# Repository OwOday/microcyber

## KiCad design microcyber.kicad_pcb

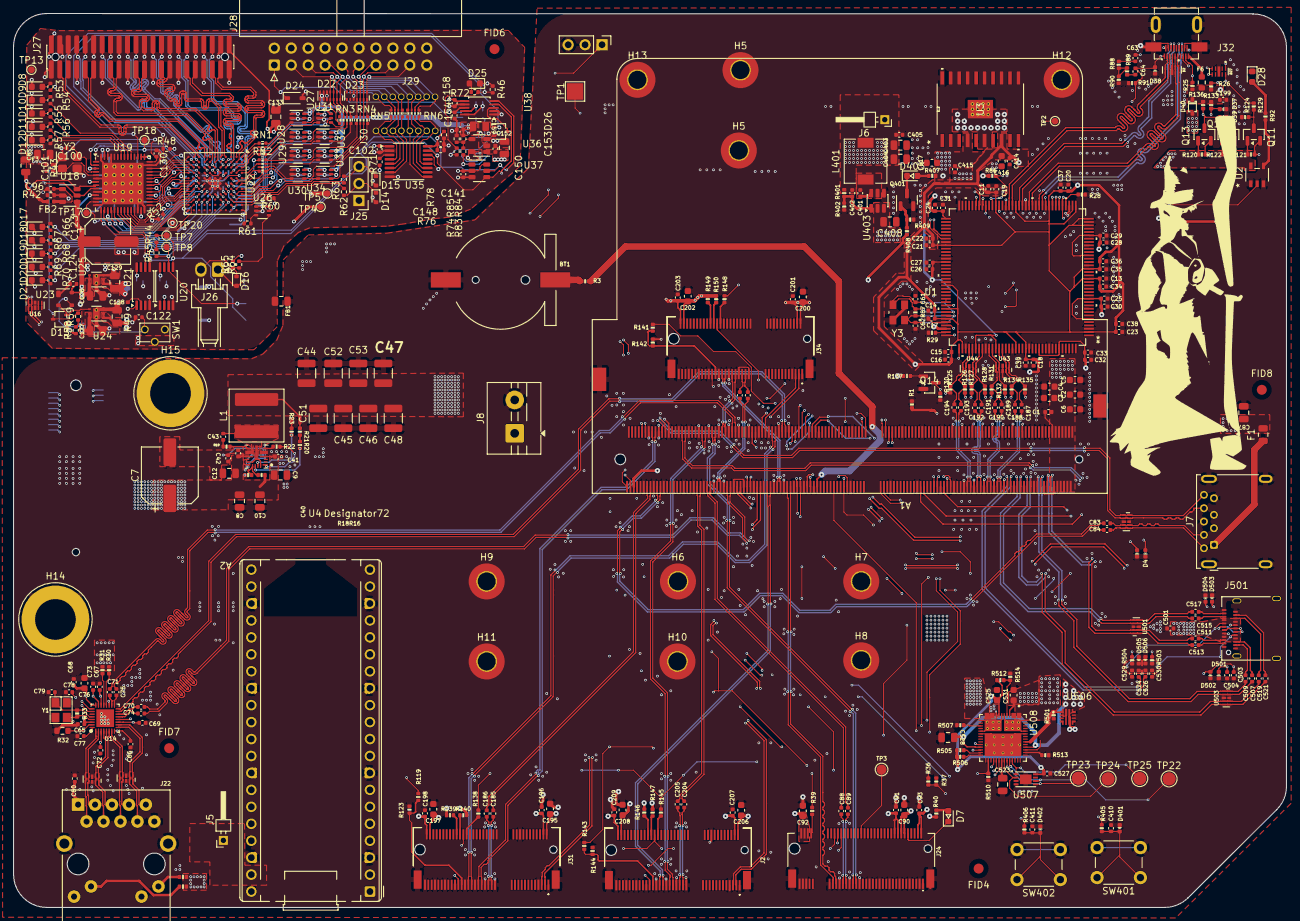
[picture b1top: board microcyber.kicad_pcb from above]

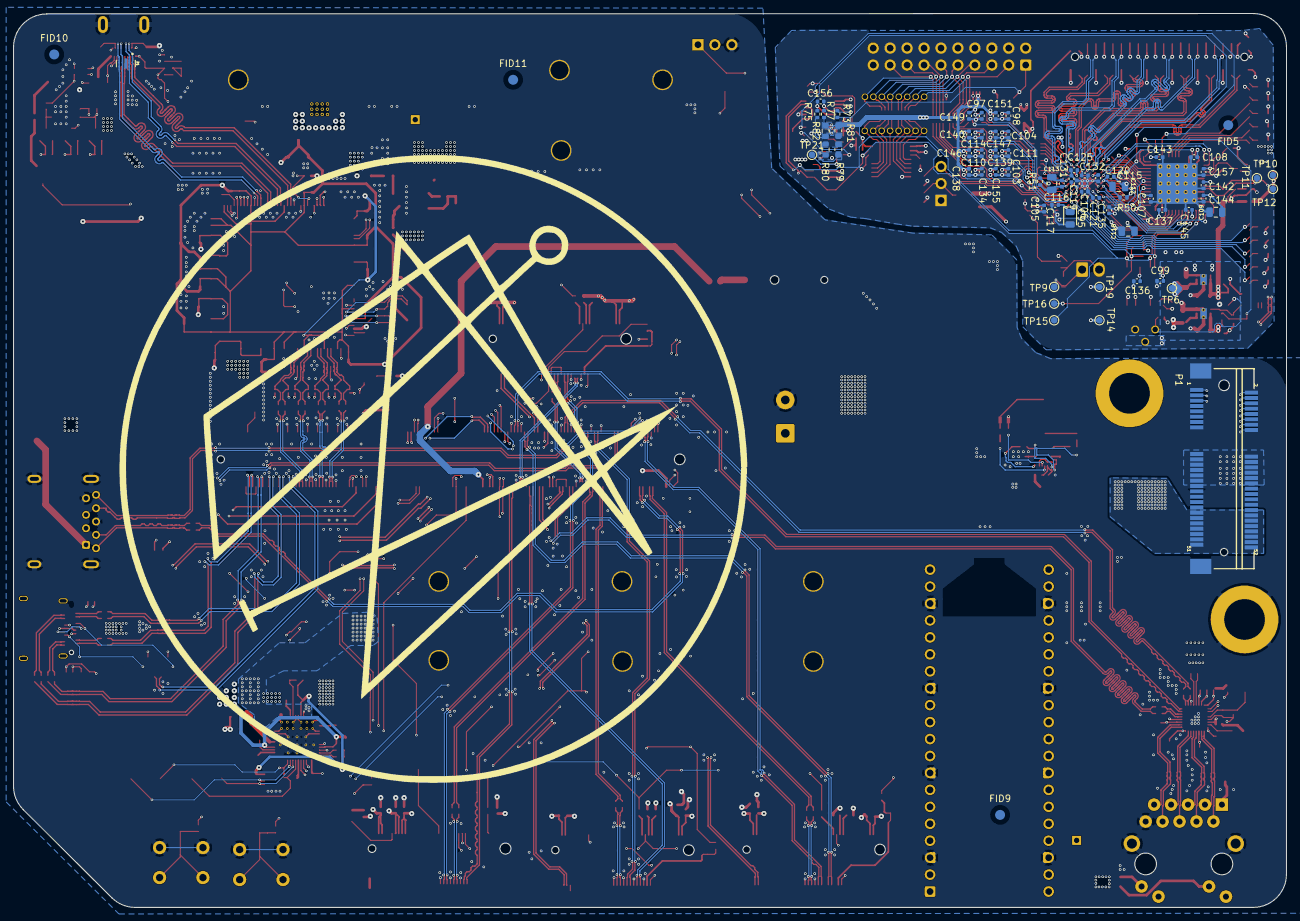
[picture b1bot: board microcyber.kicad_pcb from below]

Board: 6 copper layers, 190.8 x 134.0 mm, 497 parts (69 on the bottom side), 409 nets.

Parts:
A1: LattePanda_Mu; LattePanda_Module_H8.0mm_Horizontal
A2: RaspberryPi_Pico_W; RaspberryPi_Pico_Common_THT
BT1: Battery_Cell; Battery_Holder_CR1220_S8411-45R
C1, C43, C65, C66, C67, C68, C69, C70, C71, C72, C73, C74, C75, C77, C80, C83, C84, C91, C93, C96, C97, C98, C99, C102, C103, C104, C105, C106, C107, C108, C110, C111, C114, C115, C116, C117, C119, C120, C121, C122, C124, C125, C130, C131, C132, C134, C135, C136, C137, C138, C139, C140, C141, C142, C143, C144, C145, C146, C147, C148, C149, C150, C151, C153, C155, C156, C157, C158, C187, C188, C189, C190, C191, C192, C193, C194, C196, C198, C199, C201, C203, C207, C209, C401, C405, C414, C415, C501, C524, C526, C527: u1; C_0402_1005Metric
C2, C3, C4, C5, C6, C76, C90, C92, C195, C197, C200, C202, C206, C208: 10u; C_0603
C7: 330u; CP_Elec_8x11.9
C8, C9, C10, C12, C85, C87, C403, C404, C408, C523: 22u; C_0805_2012Metric
C11, C14, C16, C18, C20, C22, C24, C27, C29, C31, C33, C35, C37, C39: u1; C_0402
C13, C15, C17, C19, C21, C23, C25, C26, C28, C30, C32, C34, C36, C38: 10n; C_0402
C40, C41, C42, C410, C411: 1u; C_0402_1005Metric
C44, C45, C46, C47, C48, C51, C52, C53: 47u; C_1210_3225Metric
C49, C50, C88, C89, C185, C186, C204, C205, C511, C513, C519, C521: 220n; C_0402_1005Metric
C61, C62: 47p; C_0402
C63, C64: 1u; C_0402
C78, C79: 12p; C_0402_1005Metric
C95: 4u7; LED_0805_2012Metric
C100, C101: 9p; C_0402_1005Metric
C109, C112, C113, C118, C126, C127, C128, C129, C133, C152, C159, C528: 4u7; C_0805_2012Metric
C123: 150u; CP_Elec_6.3x5.9
C154: 1n 50V C0G; C_0402_1005Metric
C402, C503, C504, C529, C530: 47p; C_0402_1005Metric
C416, C417: 100u; C_0603
C507, C509, C515, C517: 330n; C_0402_1005Metric
C525, C531: 10u; C_0603_1608Metric
D1, D2, D27: RCLAMP0524PATCT; DIO_RCLAMP0524PATCT
D3, D4, D37, D38, D39: 0402ESDA-05N; D_0402_1005Metric
D7, D403: LED_G; LED_0603_1608Metric
D8, D25: GRN; LED_0603_1608Metric
D9, D19: WHT; LED_0603_1608Metric
D10, D17, D21: BLU; LED_0603_1608Metric
D11: ORA; LED_0603_1608Metric
D12: RED; LED_0603_1608Metric
D13: BAT54AW; SOT-323_SC-70
D14, D15, D16: ESD5Z5.0T1G; D_SOD-523
D18, D20: PNK; LED_0603_1608Metric
D22, D23: TPD6E05U06RVZR; UDFN-14_3.5x1.35mm_P0.5mm
D24: CDSOD323-T36S; D_SOD-323
D26: BAT54CW; SOT-323_SC-70
D28: LED; LED_0603_1608Metric
D40: 1N5819WS; D_SOD-323
D401, D402, D501, D502, D503, D504, D505, D506: ESD5V0B03; D_0402_1005Metric
F1: 6V/2A; Fuse_0805_2012Metric
F3: 6V/1A; Fuse_0805_2012Metric
F6: 6V/50mA; R_0603_1608Metric
FB1: 0; Fuse_0805_2012Metric
FB2: 600R, 0.5A; L_0402_1005Metric
FID4, FID5, FID6, FID7, FID8, FID9, FID10, FID11: Fiducial; Fiducial_1.5mm_Mask3mm
H5, H5#2, H6, H7, H8, H9, H10, H11, H12, H13: MountingHole_M2.0; MountingHole_2.7mm_Pad_TopOnly
H14, H15: MountingHole_Pad; Banana_Jack_1Pin
J1: Conn_01x03_Pin; PinHeader_1x03_P2.54mm_Vertical
J2, J31, J34: Bus_M.2_Socket_E; PCIe_M.2_Connectors_P=0.5mm_H=4.2mm_KeyE
J5, J6: Conn_01x01_Socket; PinHeader_1x01_P2.00mm_Horizontal
J7: USB3_A; USB3_A_Molex_48393-001
J8: Conn_01x02_Socket; TerminalBlock_MaiXu_MX126-5.0-02P_1x02_P5.00mm
J22: RJ45_RB1-125B8G1A; RJ45_UDE_RB1-125B8G1A
J24: Bus_M.2_Socket_M; PCIe_M.2_Connectors_P=0.5mm_H=4.2mm_KeyM
J25: AUX; PinHeader_1x03_P2.54mm_Vertical
J26: Conn_01x02; Molex_KK-254_1x02_P2.54mm_Horizontal
J27: PinHeader_2x22_P1.27mm; PinHeader_2x22_P1.27mm_Vertical__SMD
J28: IDC-Header_2x10_P2.54mm; IDC-Header_2x10_P2.54mm_Horizontal
J29, J30: Conn_01x08; PinSocket_1x08_P1.27mm_Vertical_DNP
J32: HDMI_D_1.4; HDMI_Micro-D_Molex_46765-2xxx
J501: USB_C_Receptacle; USB_C_Receptacle_Amphenol_12401610E4-2A
L1: 550nH; L_Coilcraft_XAL7070-XXX
L401: 6uH8; L_6.3x6.3_H3
NT1, NT3: NetTie_2; NetTie-2_SMD_Pad0.5mm
P1: 1775862-2; TE_1775862-2
Q11, Q401: 2N7002; SOT-23
Q12, Q13, Q14: 2SK3018; SOT-23
R1: 100K; R_0402
R3, R129: 1K; R_0402
R16: 200K; R_0402_1005Metric
R18, R401, R501, R503, R504, R507, R510: 100K; R_0402_1005Metric
R19, R20, R23, R512: 0; R_0402_1005Metric
R21: 10; R_0402_1005Metric
R22, R409, R506, R513: 10K; R_0402_1005Metric
R25, R26: 2k; R_0402
R28: 887; R_0402
R29: 500; R_0402
R30, R31, R139, R140, R146, R147, R149, R150: 10K; R_0402
R32: 2K49; R_0603_1608Metric
R33, R121: 1M; R_0402
R34, R35, R125, R126, R127, R128, R131, R132, R134, R135: 470; R_0402
R36, R119, R130, R141, R143: 0R/1%; R_0402_1005Metric
R37, R39, R123, R138, R142, R144, R145, R148: 0; R_0402
R40, R120, R122, R133, R136, R137: 2K2; R_0402
R42, R43: 5k1; R_0402_1005Metric
R44, R45, R54, R55, R60, R66, R67, R68, R69, R70, R76, R78: 2k2; R_0402_1005Metric
R46, R53, R65, R71, R74, R505: 10k; R_0402_1005Metric
R48, R52, R58, R59: 100k; R_0402_1005Metric
R49: DNP; R_0402_1005Metric_DNP
R50, R51: 100R; R_0402_1005Metric
R56, R57: 1k; R_0402_1005Metric
R61, R62, R63, R64: 47R; R_0402_1005Metric
R72: 20k; R_0402_1005Metric
R73: 470; R_0402_1005Metric
R75, R77: 4R7; R_0402_1005Metric
R79, R81: DNP; R_0603_1608Metric_DNP
R80: 0R33; R_0603_1608Metric
R82: 0R15; R_0603_1608Metric
R83: 49k9; R_0402_1005Metric
R84: 59k; R_0402_1005Metric
R85: 24k3; R_0402_1005Metric
R86: 47K; R_0402
R87: 390K; R_0402
R88, R89: 51; R_0402
R90: 5r1; R_0402
R91: 48K7; R_0402
R92: 220r; R_0402
R124: 21K5; R_0402
R402, R514: 19K1; R_0402_1005Metric
R405, R406, R407, R408: 1K; R_0402_1005Metric
RN1, RN2, RN3, RN4: 33R; R_Array_Convex_4x0402
RN5, RN6: 10k; R_Array_Convex_4x0402
SW1: RST; SW_Tactile_SPST_Angled_TC-1109DE
SW401, SW402: SW_Push; SW_PUSH_6mm
TP1: TestPoint; TestPoint_Pad_2.5x2.5mm
TP2: ALSB; TestPoint_Pad_D1.0mm
TP3: TestPoint; TestPoint_Pad_D1.5mm
TP4, TP14: 5V; TestPoint_Pad_D1.0mm
TP5, TP17, TP19: 3V3; TestPoint_Pad_D1.0mm
TP6, TP20: 1V2; TestPoint_Pad_D1.0mm
TP7, TP15: SDA; TestPoint_Pad_D1.0mm
TP8, TP16: SCL; TestPoint_Pad_D1.0mm
TP9: GND; TestPoint_Pad_D1.0mm
TP10: VBUS; TestPoint_Pad_D1.0mm
TP11: USBDM; TestPoint_Pad_D1.0mm
TP12: USBDP; TestPoint_Pad_D1.0mm
TP13: USBGND; TestPoint_Pad_D1.0mm
TP18: CLKREF; TestPoint_Pad_D1.0mm
TP21: VDAC; TestPoint_Pad_D1.0mm
TP22, TP23, TP24, TP25: TestPoint; TestPoint_Pad_D2.0mm
U1: ADV7623BSTZ; ST_144_ADI
U2: NC7SZ125M5; SC-74A-5_1P65X3P15_ONS
U3: TPPM0110DWPR; DWP20_3P81X2P79
U4: TPS548A23VANR; VAN0019A-MFG
U12, U13, U15, U16, U501, U503: ULC0524P; Diodes_UDFN-10_1.0x2.5mm_P0.5mm
U14: RTL8111H-CG-RH; QFN-32-1EP_4x4mm_P0.4mm_EP2.65x2.65mm
U18: TPD3S014; SOT-23-6
U19: CY7C68013A-56LTX; Cypress_QFN-56-1EP_8x8mm_P0.5mm_EP6.22x6.22mm_ThermalVias
U20: CAT24M01X; TSSOP-8_4.4x3mm_P0.65mm
U21: BL24C256A-SFRC; TSSOP-8_4.4x3mm_P0.65mm
U22: ICE40HX8K-BG121; BGA-121_9.0x9.0mm_Layout11x11_P0.8mm_Ball0.4mm_Pad0.35mm_NS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
U23: APX811-40UG-7; SOT-143
U24: TLV75533PDRVR; DFN-6-1EP_2x2mm_P0.65mm_EP1x1.6mm_ThermalVias
U25: TLV73312PQDRVR; DFN-6-1EP_2x2mm_P0.65mm_EP1x1.6mm_ThermalVias
U26, U27, U28, U29, U30, U31, U32, U33, U34: SN74LVC1T45DCKR; SOT-363_SC-70-6
U35: PCA6408APW; TSSOP-16_4.4x5mm_P0.65mm
U36: TPS73101DBV; SOT-23-5
U37: DAC081C081CIMK; SOT-23-6
U38: INA233; VSSOP-10_3x3mm_P0.5mm
U43, U44: TPAZ1023-04F; Diodes_UDFN-10_1.0x2.5mm_P0.5mm
U403: AP63200WU; TSOT-23-6
U506: LM73100RPWR; IC_LM73100RPWR
U507: AT25DN512C-MAHF-T; DFN-8-1EP_3x2mm_P0.5mm_EP1.75x1.45mm
U508: TPS65988DHRSHR; IC_TPS65987DDHRSHR
Y1: 25MHz; Crystal_SMD_3225-4Pin_3.2x2.5mm
Y2: 24M; Crystal_SMD_3225-4Pin_3.2x2.5mm
Y3: ABM8G-28.63636MHZ-18-D2Y-T; CRYSTAL_ABM8G_ABR

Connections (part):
5V_HDMI_VCC: C199.1, D40.1 (K), F6.1, R25.1, R26.1, R133.1, R136.1, U1.106 (5V_DETA)
+1V0: C65.2, C66.2, C67.2, C68.2, C72.2, C76.2, U14.3 (AVDD10), U14.8 (AVDD10), U14.22 (DVDD10), U14.24 (REGOUT), U14.30 (AVDD10)
+1V2_glasgow: C118.1, C119.1, C120.1, C121.1, C125.1, C129.1, R50.2, R51.2, TP6.1 (1_1), TP20.1 (1_1), U22.D4 (VCC), U22.D8 (VCC), U22.H4 (VCC), U22.H8 (VCC), U25.1 (OUT), U25.2 (NC)
+1V8: C11.1, C13.1, C14.1, C15.1, C16.1, C17.1, C18.1, C19.1, C20.1, C21.1, C22.1, C23.1, C34.1, C35.1, C36.1, C37.1, C38.1, C39.1, C414.2, C416.1, U1.2 (CVDD), U1.18 (DVDD), U1.21 (CVDD), U1.34 (CVDD), U1.36 (TXPVDD), U1.37 (TXPLVDD), U1.45 (TXAVDD), U1.55 (TXAVDD), U1.61 (DVDD), U1.81 (DVDD), U1.93 (DVDD), U1.100 (PVDD), U1.103 (PVDD), U1.110 (CVDD), U1.126 (DVDD), U1.129 (CVDD), U3.8 (1.8VOUT)
+3V3: C24.1, C25.1, C26.1, C27.1, C28.1, C29.1, C30.1, C31.1, C32.1, C33.1, C415.2, C417.1, Q11.1 (G), Q12.1 (G), Q13.1 (G), R86.2, R120.1, R121.1, R122.1, R407.2, U1.6 (TVDD), U1.12 (TVDD), U1.25 (TVDD), U1.31 (TVDD), U1.73 (DVDDIO), U1.86 (DVDDIO), U1.114 (TVDD), U1.120 (TVDD), U1.133 (TVDD), U1.139 (TVDD), U2.5 (VCC), U3.4 (3.3VOUT)
+3V3_TPS: C525.2, C527.2, R505.2, R506.2, R512.1, U507.8 (VCC), U508.9 (LDO_3V3)
+3V3_glasgow: C95.1, C97.1, C98.1, C99.1, C102.1, C103.1, C104.1, C105.1, C106.1, C107.1, C108.1, C109.1, C110.1, C111.1, C114.1, C117.1, C128.1, C131.1, C134.1, C135.1, C136.1, C137.1, C142.1, C143.1, C144.1, C145.1, C150.1, C157.1, C158.1, D13.2, J27.2, R44.2, R45.2, R48.2, R49.2, R53.1, R58.1, R65.2, R71.2, TP5.1 (1_1), TP19.1 (1_1), U19.3 (AVCC), U19.7 (AVCC), U19.11 (VCC), U19.17 (VCC), U19.27 (VCC), U19.32 (VCC), U19.43 (VCC), U19.44 (WAKEUP), U19.55 (VCC), U20.2 (A1), U20.8 (VCC), U21.1 (A0), U21.8 (VCC), U22.C10 (VPP_2V5), U22.D6 (VCCIO_0), U22.F8 (VCCIO_1), U22.H6 (VCCIO_2), U22.L11 (VCC_SPI), U24.1 (OUT), U24.2 (NC), U26.1 (VCCA), U26.6 (VCCB), U27.1 (VCCA), U28.1 (VCCA), U29.1 (VCCA), U30.1 (VCCA), U31.1 (VCCA), U32.1 (VCCA), U33.1 (VCCA), U34.1 (VCCA), U35.1 (VDD_I2C), U37.2 (VA), U37.6 (ADR0), U38.6 (VS)
+3V3_highpower: C44.2, C45.2, C46.2, C47.2, C48.2, C51.2, C52.2, C53.2, C69.2, C73.2, C77.2, C90.2, C91.2, C92.2, C93.2, C195.2, C196.2, C197.2, C198.1, C200.2, C201.2, C202.2, C203.2, C206.2, C207.2, C208.2, C209.2, C531.2, J2.2 (3.3V), J2.4 (3.3V), J2.72 (3.3V), J2.74 (3.3V), J24.2 (3.3V), J24.4 (3.3V), J24.12 (3.3V), J24.14 (3.3V), J24.16 (3.3V), J24.18 (3.3V), J24.70 (3.3V), J24.72 (3.3V), J24.74 (3.3V), J31.2 (3.3V), J31.4 (3.3V), J31.72 (3.3V), J31.74 (3.3V), J34.2 (3.3V), J34.4 (3.3V), J34.72 (3.3V), J34.74 (3.3V), L1.2, NT1.2, R30.1, R31.1, R34.2, R35.2, R40.2, R139.2, R140.1, R146.2, R147.1, R149.2, R150.1, U14.11 (AVDD33), U14.23 (VDDREG), U14.32 (AVDD33), U508.5 (VIN_3V3)
+5V: C85.2, C87.2, C402.1, C403.2, C404.2, C405.1, C528.2, D40.2 (A), F1.1, F3.1, J6.1 (Pin_1_1), L401.2, R401.2, U3.6 (5VCC), U506.5 (IN), U508.25 (PP1_CABLE), U508.46 (PP2_CABLE)
+5V_glasgow: C123.1, C124.1, C126.2, C127.2, C152.1, C153.1, TP4.1 (1_1), TP14.1 (1_1), U18.4 (OUT), U23.4 (VCC), U24.5 (NC), U24.6 (IN), U25.4 (EN), U25.5 (NC), U25.6 (IN), U36.1 (IN)
+12V: A1.250 (VIN), A1.251 (VIN), A1.252 (VIN), A1.253 (VIN), A1.254 (VIN), A1.255 (VIN), A1.256 (VIN), A1.257 (VIN), A1.258 (VIN), A1.259 (VIN), A1.260 (VIN), C1.1, C2.2, C3.2, C4.2, C5.2, C6.2, C7.1, C8.1, C9.1, C10.1, C12.1, C40.1, C41.1, C408.2, H15.1 (1_1), P1.38 (USB_D+/RES), P1.39 (+3.3VAUX/+3.3V3), P1.40 (GND10), P1.41 (+3.3VAUX/+3.3V4), P1.42 (~LED_WWAN/RES), P1.43 (GND/NC), P1.44 (~LED_WLAN/RES), P1.45 (RES/VENDOR1), P1.46 (~LED_WPAN/RES), P1.47 (RES/VENDOR2), P1.48 (+1.5V2), P1.49 (RES/DA/DSS), P1.50 (GND12), P1.51 (RES/DETECT), P1.52 (+3.3VAUX/+3.3V5), R16.1, U4.4 (VIN), U4.12 (VIN), U403.2 (EN), U403.3 (IN)
+BATT: A1.115 (VBAT), R3.1
/CLKREQ3: A1.100 (~CLKREQ3), R36.1, R119.1, R141.1, R143.1
/Ethernet/GbE_PCIe_CLK+: A1.94 (REFCLK4+), U14.15 (REFCLK_P)
/Ethernet/GbE_PCIe_CLK-: A1.96 (REFCLK4-), U14.16 (REFCLK_N)
/Ethernet/GbE_PCIe_RX+: A1.64 (HSIO6_RX+), C75.2
/Ethernet/GbE_PCIe_RX-: A1.66 (HSIO6_RX-), C71.2
/Ethernet/GbE_PCIe_TX+: A1.61 (HSIO6_TX+), C74.2
/Ethernet/GbE_PCIe_TX-: A1.63 (HSIO6_TX-), C70.2
/Ethernet/HSI+: C74.1, U14.13 (HSIP)
/Ethernet/HSI-: C70.1, U14.14 (HSIN)
/Ethernet/HSO+: C75.1, U14.17 (HSOP)
/Ethernet/HSO-: C71.1, U14.18 (HSON)
/Ethernet/LED1_1000: J22.L4, U14.26 (LED1)
/Ethernet/LED2_ACT: J22.L2, U14.25 (LED2)
/Ethernet/MDI0+: J22.R2 (TD1+), U13.5, U13.6 (NC), U14.1 (MDIP0)
/Ethernet/MDI0-: J22.R3 (TD1-), U13.4, U13.7 (NC), U14.2 (MDIN0)
/Ethernet/MDI1+: J22.R4 (TD2+), U13.2, U13.9 (NC), U14.4 (MDIP1)
/Ethernet/MDI1-: J22.R5 (TD2-), U13.1, U13.10 (NC), U14.5 (MDIN1)
/Ethernet/MDI2+: J22.R6 (TD3+), U12.5, U12.6 (NC), U14.6 (MDIP2)
/Ethernet/MDI2-: J22.R7 (TD3-), U12.4, U12.7 (NC), U14.7 (MDIN2)
/Ethernet/MDI3+: J22.R8 (TD4+), U12.2, U12.9 (NC), U14.9 (MDIP3)
/Ethernet/MDI3-: J22.R9 (TD4-), U12.1, U12.10 (NC), U14.10 (MDIN3)
/Ethernet/~CLKREQ4: A1.102 (~CLKREQ4), U14.12 (CLKREQB)
/GPIO_1: A2.21 (GPIO16), P1.4 (GND2)
/GPIO_2: A2.22 (GPIO17), P1.6 (1.5V/+1.5V)
/GPIO_3: A2.24 (GPIO18), P1.8 (UIM_PWR/RES)
/GPIO_4: A2.25 (GPIO19), P1.10 (UIM_DATA/RES)
/GPIO_5: A2.26 (GPIO20), P1.12 (UIM_CLK/RES)
/GPIO_6: A2.27 (GPIO21), P1.14 (UIM_RESET/RES)
/GPIO_7: A2.29 (GPIO22), P1.16 (UIM_VPP/RES)
/GPIO_8: A2.20 (GPIO15), P1.2 (3.3VAUX/+3.3V1)
/HDMI/CEC_STUB: D27.5, J32.15 (CEC)
/HDMI/DDC_SCL: D27.6, D37.2 (A2), J32.17 (SCL), Q12.3 (D), R25.2, R133.2, U1.43 (TXDDC_SDA), U1.109 (DDCA_SCL)
/HDMI/DDC_SDA: D27.1, D39.2 (A2), J32.18 (SDA), Q13.3 (D), R26.2, R136.2, U1.44 (TXDDC_SCL), U1.108 (DDCA_SDA)
/HDMI/DDI_B_DDC_SCL: A1.171 (DDIB_DDC_SCL), Q12.2 (S), R122.2
/HDMI/DDI_B_DDC_SDA: A1.169 (DDIB_DDC_SDA), Q13.2 (S), R120.2
/HDMI/DDI_B_HPD: A1.183 (DDIB_HPD), Q11.2 (S), R121.2
/HDMI/DDI_B_TX0+: A1.217 (DDIB_TX0+), C187.1
/HDMI/DDI_B_TX0-: A1.215 (DDIB_TX0-), C188.1
/HDMI/DDI_B_TX1+: A1.211 (DDIB_TX1+), C189.1
/HDMI/DDI_B_TX1-: A1.209 (DDIB_TX1-), C190.1
/HDMI/DDI_B_TX2+: A1.205 (DDIB_TX2+), C191.1
/HDMI/DDI_B_TX2-: A1.203 (DDIB_TX2-), C192.1
/HDMI/DDI_B_TX3+: A1.199 (DDIB_TX3+), C193.1
/HDMI/DDI_B_TX3-: A1.197 (DDIB_TX3-), C194.1
/HDMI/HDMI_TX0+: D2.2, D2.9, J32.9 (D0+), U1.51 (TX0+)
/HDMI/HDMI_TX0-: D2.1, D2.10, J32.11 (D0-), U1.50 (TX0-)
/HDMI/HDMI_TX1+: D1.1, D1.10, J32.6 (D1+), U1.54 (TX1+)
/HDMI/HDMI_TX1-: D1.2, D1.9, J32.8 (D1-), U1.53 (TX1-)
/HDMI/HDMI_TX2+: D2.5, D2.6, J32.3 (D2+), U1.57 (TX2+)
/HDMI/HDMI_TX2-: D2.4, D2.7, J32.5 (D2-), U1.56 (TX2-)
/HDMI/HDMI_TXC+: D1.4, D1.7, J32.12 (CK+), U1.48 (TXC+)
/HDMI/HDMI_TXC-: D1.5, D1.6, J32.14 (CK-), U1.47 (TXC-)
/HDMI/HDMI_TX_RESERVED: C63.2, J32.2 (UTILITY/HEAC+), U1.42 (ARC+)
/HDMI/HPD: C64.2, D27.10, D38.2 (A2), J32.1 (HPD/HEAC-), R91.1, R129.2, U1.41 (HPD_ARC-), U1.105 (HP_CTRLA), U2.2 (A)
/HDMI/OSD_CS: A2.2 (GPIO1), U1.65 (EP_CS)
/HDMI/OSD_MISO: A2.5 (GPIO3), U1.67 (EP_MISO)
/HDMI/OSD_MOSI: A2.1 (GPIO0), U1.66 (EP_MOSI)
/HDMI/OSD_SCK: A2.4 (GPIO2), U1.64 (EP_SCK)
/HDMI/SCL: A1.146 (I2C4_SCL), U1.79 (SCL)
/HDMI/SDA: A1.148 (I2C4_SDA), U1.78 (SDATA)
/HDMI/TMDS_CK+: C193.2, R126.1, U1.113 (RXA_C+), U44.4, U44.7 (NC)
/HDMI/TMDS_CK-: C194.2, R125.1, U1.112 (RXA_C-), U44.5, U44.6 (NC)
/HDMI/TMDS_D0+: C191.2, R128.1, U1.116 (RXA_0+), U44.1, U44.10 (NC)
/HDMI/TMDS_D0-: C192.2, R127.1, U1.115 (RXA_0-), U44.2, U44.9 (NC)
/HDMI/TMDS_D1+: C189.2, R132.1, U1.119 (RXA_1+), U43.4, U43.7 (NC)
/HDMI/TMDS_D1-: C190.2, R131.1, U1.118 (RXA_1-), U43.5, U43.6 (NC)
/HDMI/TMDS_D2+: C187.2, R135.1, U1.122 (RXA_2+), U43.1, U43.10 (NC)
/HDMI/TMDS_D2-: C188.2, R134.1, U1.121 (RXA_2-), U43.2, U43.9 (NC)
/LattePanda_Module/HSIO_0_RX+: A1.18 (HSIO0_RX-), J31.41 (PERp0)
/LattePanda_Module/HSIO_0_RX-: A1.16 (HSIO0_RX+), J31.43 (PERn0)
/LattePanda_Module/HSIO_0_TX+: A1.15 (HSIO0_TX-), C185.1
/LattePanda_Module/HSIO_0_TX-: A1.13 (HSIO0_TX+), C186.1
/LattePanda_Module/HSIO_1_TX+: A1.19 (HSIO1_TX+), C84.1
/LattePanda_Module/HSIO_1_TX-: A1.21 (HSIO1_TX-), C83.1
/LattePanda_Module/HSIO_9_RX+: A1.48 (HSIO9_RX-), J2.41 (PERp0)
/LattePanda_Module/HSIO_9_RX-: A1.46 (HSIO9_RX+), J2.43 (PERn0)
/LattePanda_Module/HSIO_9_TX+: A1.45 (HSIO9_TX-), C204.1
/LattePanda_Module/HSIO_9_TX-: A1.43 (HSIO9_TX+), C205.1
/LattePanda_Module/HSIO_10_RX+: A1.52 (HSIO10_RX+), J24.43 (PERp0/SATA-B-)
/LattePanda_Module/HSIO_10_RX-: A1.54 (HSIO10_RX-), J24.41 (PERn0/SATA-B+)
/LattePanda_Module/HSIO_10_TX+: A1.49 (HSIO10_TX+), C88.1
/LattePanda_Module/HSIO_10_TX-: A1.51 (HSIO10_TX-), C89.1
/LattePanda_Module/HSIO_11_RX+: A1.60 (HSIO11_RX-), J34.41 (PERp0)
/LattePanda_Module/HSIO_11_RX-: A1.58 (HSIO11_RX+), J34.43 (PERn0)
/LattePanda_Module/HSIO_11_TX+: A1.57 (HSIO11_TX-), C49.1
/LattePanda_Module/HSIO_11_TX-: A1.55 (HSIO11_TX+), C50.1
/LattePanda_Module/I2C3_SCL: A1.150 (I2C3_SCL), A2.7 (GPIO5)
/LattePanda_Module/I2C3_SDA: A1.152 (I2C3_SDA), A2.6 (GPIO4)
/LattePanda_Module/PMCALERT: A1.125 (GPP_B11), U508.34 (~I2C2_IRQ)
/LattePanda_Module/REFCLK0+: A1.87 (REFCLK0-), J2.47 (REFCLKp0)
/LattePanda_Module/REFCLK0-: A1.85 (REFCLK0+), J2.49 (REFCLKn0)
/LattePanda_Module/REFCLK1+: A1.93 (REFCLK1-), J34.47 (REFCLKp0)
/LattePanda_Module/REFCLK1-: A1.91 (REFCLK1+), J34.49 (REFCLKn0)
/LattePanda_Module/REFCLK2+: A1.97 (REFCLK2+), J24.55 (REFCLKp)
/LattePanda_Module/REFCLK2-: A1.99 (REFCLK2-), J24.53 (REFCLKn)
/LattePanda_Module/REFCLK3+: A1.90 (REFCLK3-), J31.47 (REFCLKp0)
/LattePanda_Module/REFCLK3-: A1.88 (REFCLK3+), J31.49 (REFCLKn0)
/LattePanda_Module/SMB_ALERT: A1.104 (~SMB_ALERT), P1.5 (COEX2/RES)
/LattePanda_Module/SMB_CLK: A1.106 (SMB_CLK), P1.3 (COEX1/RES)
/LattePanda_Module/SMB_DATA: A1.108 (SMB_DATA), P1.1 (~WAKE/RES)
/LattePanda_Module/SML1CLK: A1.147 (SML1_CLK), U508.32 (I2C2_SCL)
/LattePanda_Module/SML1DATA: A1.145 (SML1_DATA), U508.33 (I2C2_SDA)
/LattePanda_Module/TCP1_AUX+: A1.223 (TCP0_AUX+), C524.1
/LattePanda_Module/TCP1_AUX-: A1.221 (TCP0_AUX-), C526.1
/LattePanda_Module/TCP1_DDC_SCL: A1.179 (TCP0_DDC_SCL), R503.1
/LattePanda_Module/TCP1_DDC_SDA: A1.177 (TCP0_DDC_SDA), R504.1
/LattePanda_Module/TCP1_HPD: A1.187 (TCP0_HPD), R510.1, U508.30 (GPIO3(HPD1))
/LattePanda_Module/USB_2_P3+: A1.81 (USB2_P3+), J2.3 (USB_D+)
/LattePanda_Module/USB_2_P3-: A1.79 (USB2_P3-), J2.5 (USB_D-)
/LattePanda_Module/USB_2_P7+: A1.76 (USB2_P7+), J31.3 (USB_D+)
/LattePanda_Module/USB_2_P7-: A1.78 (USB2_P7-), J31.5 (USB_D-)
/LattePanda_Module/USB_2_P8+: A1.82 (USB2_P8+), J34.3 (USB_D+)
/LattePanda_Module/USB_2_P8-: A1.84 (USB2_P8-), J34.5 (USB_D-)
/LattePanda_Module/~PWR_SW: A1.1 (~PWRBTN), R405.2
/LattePanda_Module/~RST_SW: A1.3 (~RSTBTN), R406.2
/M2_EKEY/CON_PCIE_TX_0+: C185.2, J31.35 (PETp0)
/M2_EKEY/CON_PCIE_TX_0-: C186.2, J31.37 (PETn0)
/M2_EKEY/CON_PCIE_TX_1+: C204.2, J2.35 (PETp0)
/M2_EKEY/CON_PCIE_TX_1-: C205.2, J2.37 (PETn0)
/M2_EKEY/CON_PCIE_TX_2+: C49.2, J34.35 (PETp0)
/M2_EKEY/CON_PCIE_TX_2-: C50.2, J34.37 (PETn0)
/M2_MKEY/CON_PCIE_TX_1+: C88.2, J24.49 (PETp0/SATA-A+)
/M2_MKEY/CON_PCIE_TX_1-: C89.2, J24.47 (PETn0/SATA-A-)
/PSU/5agnd: U4.14 (CFG4), U4.19 (AGND)
/PSU/5vcc: C42.2, R22.2, U4.6 (VCC), U4.13 (CFG3), U4.15 (CFG5)
/SUSCLK: A1.131 (SUSCLK), R39.2, R138.2, R145.2, R148.2
/USB_2_3/CON_USB1_D_N: A1.73 (USB2_P2-), TP11.1 (1_1), U16.2, U16.9 (NC), U18.5 (D1), U19.9 (D-)
/USB_2_3/CON_USB1_D_P: A1.75 (USB2_P2+), TP12.1 (1_1), U16.1, U16.10 (NC), U18.6 (D2), U19.8 (D+)
/USB_2_3/CON_USB4_D_N: A1.67 (USB2_P1-), D4.2 (A2), J7.2 (D-)
/USB_2_3/CON_USB4_D_P: A1.69 (USB2_P1+), D3.2 (A2), J7.3 (D+)
/USB_2_3/CON_USB4_SSRX_N: A1.24 (HSIO1_RX-), J7.5 (SSRX-), U15.1, U15.10 (NC)
/USB_2_3/CON_USB4_SSRX_P: A1.22 (HSIO1_RX+), J7.6 (SSRX+), U15.2, U15.9 (NC)
/USB_2_3/CON_USB4_SSTX_N: C83.2, J7.8 (SSTX-), U15.4, U15.7 (NC)
/USB_2_3/CON_USB4_SSTX_P: C84.2, J7.9 (SSTX+), U15.5, U15.6 (NC)
/USB_2_3/EXT_VBUS_SOURCE1: R501.2, U506.1 (EN/UVLO), U508.48 (GPIO16(PP_EXT1))
/USB_2_3/USBC1_CC1: C504.1, D501.2 (A2), J501.A5 (CC1), U508.24 (C1_CC1)
/USB_2_3/USBC1_CC2: C503.1, D502.2 (A2), J501.B5 (CC2), U508.26 (C1_CC2)
/USB_2_3/USBC1_CONN_RX1+: C509.1, J501.B11 (RX1+)
/USB_2_3/USBC1_CONN_RX1-: C507.1, J501.B10 (RX1-)
/USB_2_3/USBC1_CONN_RX2+: C517.1, J501.A11 (RX2+)
/USB_2_3/USBC1_CONN_RX2-: C515.1, J501.A10 (RX2-)
/USB_2_3/USBC1_CONN_TX1+: C513.1, J501.A2 (TX1+)
/USB_2_3/USBC1_CONN_TX1-: C511.1, J501.A3 (TX1-)
/USB_2_3/USBC1_CONN_TX2+: C521.1, J501.B2 (TX2+)
/USB_2_3/USBC1_CONN_TX2-: C519.1, J501.B3 (TX2-)
/USB_2_3/USBC1_SBU1: C524.2, C529.1, D505.2 (A2), J501.A8 (SBU1), R504.2
/USB_2_3/USBC1_SBU2: C526.2, C530.1, D506.2 (A2), J501.B8 (SBU2), R503.2
/USB_2_3/USBC1_TX0_D+: A1.247 (TCP0_TX0+), C513.2, U501.1, U501.10 (NC)
/USB_2_3/USBC1_TX0_D-: A1.245 (TCP0_TX0-), C511.2, U501.2, U501.9 (NC)
/USB_2_3/USBC1_TX1_D+: A1.235 (TCP0_TX1+), C521.2, U503.5, U503.6 (NC)
/USB_2_3/USBC1_TX1_D-: A1.233 (TCP0_TX1-), C519.2, U503.4, U503.7 (NC)
/USB_2_3/USBC1_TXRX0_D+: A1.241 (TCP0_TXRX0+), C509.2, U503.1, U503.10 (NC)
/USB_2_3/USBC1_TXRX0_D-: A1.239 (TCP0_TXRX0-), C507.2, U503.2, U503.9 (NC)
/USB_2_3/USBC1_TXRX1_D+: A1.229 (TCP0_TXRX1+), C517.2, U501.5, U501.6 (NC)
/USB_2_3/USBC1_TXRX1_D-: A1.227 (TCP0_TXRX1-), C515.2, U501.4, U501.7 (NC)
/USB_2_3/USBC1_USB2_D+: A1.112 (USB2_P6+), D503.2 (A2), J501.A6 (D+), J501.B6 (D+)
/USB_2_3/USBC1_USB2_D-: A1.114 (USB2_P6-), D504.2 (A2), J501.A7 (D-), J501.B7 (D-)
/USB_2_3/USBC1_VBUS: C501.1, J501.A4 (VBUS), J501.A9 (VBUS), J501.B4 (VBUS), J501.B9 (VBUS), U506.6 (OUT), U508.13 (VBUS1)
/USB_2_3/VCHARGE: J8.1, U508.1 (PP_HV2), U508.11 (PP_HV1)
/glasgow/A0: U19.37 (PA4/FIOADDR0), U22.K3 (IOB_63)
/glasgow/A1: U19.38 (PA5/FIOADDR1), U22.L2 (IOB_61)
/glasgow/CLKIF: TP17.1 (1_1), U19.13 (IFCLK), U22.K6 (IOB_82_GBIN4)
/glasgow/CLKREF: TP18.1 (1_1), U19.54 (CLKOUT), U22.D5 (IOT_212), U22.L5 (IOB_81_GBIN5)
/glasgow/D0: U19.18 (PB0/FD0), U22.H7 (IOB_87)
/glasgow/D1: U19.19 (PB1/FD1), U22.J7 (IOB_86)
/glasgow/D2: U19.20 (PB2/FD2), U22.J9 (IOB_106_SDI)
/glasgow/D3: U19.21 (PB3/FD3), U22.K10 (IOB_108_SS)
/glasgow/D4: U19.22 (PB4/FD4), U22.L10 (IOB_107_SCK)
/glasgow/D5: U19.23 (PB5/FD5), U22.K9 (IOB_105_SDO)
/glasgow/D6: U19.24 (PB6/FD6), U22.L8 (IOB_103_CBSEL0)
/glasgow/D7: U19.25 (PB7/FD7), U22.K7 (IOB_89)
/glasgow/ENVA: R46.1, R72.1, R74.2, U19.45 (PD0/FD8)
/glasgow/FLAGA: U19.29 (CTL0/FLAGA), U22.L7 (IOB_94)
/glasgow/FLAGB: U19.30 (CTL1/FLAGB), U22.K5 (IOB_79)
/glasgow/FLAGC: U19.31 (CTL2/FLAGC), U22.L4 (IOB_72)
/glasgow/FLAGD: U19.40 (PA7/FLAGD/~SLCS), U22.J3 (IOB_57)
/glasgow/FPGA_DONE: U19.36 (PA3/WU2), U22.K8 (CDONE)
/glasgow/GNDPLL0: C112.2, C115.2, U22.L6 (GNDPLL0)
/glasgow/GNDPLL1: C113.2, C116.2, U22.C5 (GNDPLL1)
/glasgow/IO_Banks/DA0: U22.C7 (IOT_191), U27.5 (DIR)
/glasgow/IO_Banks/DA1: U22.C8 (IOT_179), U31.5 (DIR)
/glasgow/IO_Banks/DA2: U22.D7 (IOT_181), U28.5 (DIR)
/glasgow/IO_Banks/DA3: U22.A7 (IOT_192), U32.5 (DIR)
/glasgow/IO_Banks/DA4: U22.B8 (IOT_177), U29.5 (DIR)
/glasgow/IO_Banks/DA5: U22.A8 (IOT_190), U33.5 (DIR)
/glasgow/IO_Banks/DA6: U22.B9 (IOT_174), U30.5 (DIR)
/glasgow/IO_Banks/DA7: U22.A9 (IOT_178), U34.5 (DIR)
/glasgow/IO_Banks/IO_Buffer_A/ISNS_H: R75.1, R79.2, R80.2, R81.1, R82.1
/glasgow/IO_Banks/IO_Buffer_A/P0: J30.1, RN5.5 (R4.2), U35.4 (P0)
/glasgow/IO_Banks/IO_Buffer_A/P1: J30.2, RN5.6 (R3.2), U35.5 (P1)
/glasgow/IO_Banks/IO_Buffer_A/P2: J30.3, RN5.7 (R2.2), U35.6 (P2)
/glasgow/IO_Banks/IO_Buffer_A/P3: J30.4, RN5.8 (R1.2), U35.7 (P3)
/glasgow/IO_Banks/IO_Buffer_A/P4: J30.5, RN6.5 (R4.2), U35.9 (P4)
/glasgow/IO_Banks/IO_Buffer_A/P5: J30.6, RN6.6 (R3.2), U35.10 (P5)
/glasgow/IO_Banks/IO_Buffer_A/P6: J30.7, RN6.7 (R2.2), U35.11 (P6)
/glasgow/IO_Banks/IO_Buffer_A/P7: J30.8, RN6.8 (R1.2), U35.12 (P7)
/glasgow/IO_Banks/IO_Buffer_A/VDAC: R83.1, TP21.1 (1_1), U37.1 (VOUT)
/glasgow/IO_Banks/IO_Buffer_A/VFB: R83.2, R84.1, R85.2, U36.4 (FB)
/glasgow/IO_Banks/IO_Buffer_A/VIO_EN: D26.2, R74.1, U36.3 (EN)
/glasgow/IO_Banks/IO_Buffer_A/VSENSE: D24.1 (K), J28.1, R73.2
/glasgow/IO_Banks/IO_Buffer_A/X0: RN1.8 (R1.2), U27.3 (A)
/glasgow/IO_Banks/IO_Buffer_A/X1: RN1.7 (R2.2), U31.3 (A)
/glasgow/IO_Banks/IO_Buffer_A/X2: RN1.6 (R3.2), U28.3 (A)
/glasgow/IO_Banks/IO_Buffer_A/X3: RN1.5 (R4.2), U32.3 (A)
/glasgow/IO_Banks/IO_Buffer_A/X4: RN2.8 (R1.2), U29.3 (A)
/glasgow/IO_Banks/IO_Buffer_A/X5: RN2.7 (R2.2), U33.3 (A)
/glasgow/IO_Banks/IO_Buffer_A/X6: RN2.6 (R3.2), U30.3 (A)
/glasgow/IO_Banks/IO_Buffer_A/X7: RN2.5 (R4.2), U34.3 (A)
/glasgow/IO_Banks/IO_Buffer_A/Y0: RN3.1 (R1.1), U27.4 (B)
/glasgow/IO_Banks/IO_Buffer_A/Y1: RN3.2 (R2.1), U31.4 (B)
/glasgow/IO_Banks/IO_Buffer_A/Y2: RN3.3 (R3.1), U28.4 (B)
/glasgow/IO_Banks/IO_Buffer_A/Y3: RN3.4 (R4.1), U32.4 (B)
/glasgow/IO_Banks/IO_Buffer_A/Y4: RN4.1 (R1.1), U29.4 (B)
/glasgow/IO_Banks/IO_Buffer_A/Y5: RN4.2 (R2.1), U33.4 (B)
/glasgow/IO_Banks/IO_Buffer_A/Y6: RN4.3 (R3.1), U30.4 (B)
/glasgow/IO_Banks/IO_Buffer_A/Y7: RN4.4 (R4.1), U34.4 (B)
/glasgow/IO_Banks/IO_Buffer_A/Z0: D22.4 (N/C), D22.11 (Ch4), J28.3, J29.1, RN3.8 (R1.2), RN5.4 (R4.1)
/glasgow/IO_Banks/IO_Buffer_A/Z1: D22.3 (N/C), D22.12 (Ch3), J28.5, J29.2, RN3.7 (R2.2), RN5.3 (R3.1)
/glasgow/IO_Banks/IO_Buffer_A/Z2: D22.2 (N/C), D22.13 (Ch2), J28.7, J29.3, RN3.6 (R3.2), RN5.2 (R2.1)
/glasgow/IO_Banks/IO_Buffer_A/Z3: D22.1 (N/C), D22.14 (Ch1), J28.9, J29.4, RN3.5 (R4.2), RN5.1 (R1.1)
/glasgow/IO_Banks/IO_Buffer_A/Z4: D23.4 (N/C), D23.11 (Ch4), J28.11, J29.5, RN4.8 (R1.2), RN6.4 (R4.1)
/glasgow/IO_Banks/IO_Buffer_A/Z5: D23.3 (N/C), D23.12 (Ch3), J28.13, J29.6, RN4.7 (R2.2), RN6.3 (R3.1)
/glasgow/IO_Banks/IO_Buffer_A/Z6: D23.2 (N/C), D23.13 (Ch2), J28.15, J29.7, RN4.6 (R3.2), RN6.2 (R2.1)
/glasgow/IO_Banks/IO_Buffer_A/Z7: D23.1 (N/C), D23.14 (Ch1), J28.17, J29.8, RN4.5 (R4.2), RN6.1 (R1.1)
/glasgow/IO_Banks/QA0: RN1.1 (R1.1), U22.A1 (IOT_225)
/glasgow/IO_Banks/QA1: RN1.2 (R2.1), U22.A2 (IOT_222)
/glasgow/IO_Banks/QA2: RN1.3 (R3.1), U22.B3 (IOT_221)
/glasgow/IO_Banks/QA3: RN1.4 (R4.1), U22.A3 (IOT_223)
/glasgow/IO_Banks/QA4: RN2.1 (R1.1), U22.B5 (IOT_208), U22.B6 (IOT_198_GBIN0)
/glasgow/IO_Banks/QA5: RN2.2 (R2.1), U22.A4 (IOT_211)
/glasgow/IO_Banks/QA6: RN2.3 (R3.1), U22.A6 (IOT_206), U22.B7 (IOT_197_GBIN1)
/glasgow/IO_Banks/QA7: RN2.4 (R4.1), U22.A5 (IOT_207)
/glasgow/IO_Banks/U1: R66.1, U22.G9 (IOR_128)
/glasgow/IO_Banks/U2: R67.1, U22.G8 (IOR_118)
/glasgow/IO_Banks/U3: R68.1, U22.E9 (IOR_144)
/glasgow/IO_Banks/U4: R69.1, U22.D9 (IOR_147)
/glasgow/IO_Banks/U5: R70.1, U22.E8 (IOR_146)
/glasgow/IO_Banks/VIOA: C138.1, C139.1, C140.1, C141.1, C146.1, C147.1, C148.1, C149.1, C151.1, C155.1, C159.1, D22.6 (N/C), D22.7 (N/C), D22.8 (Ch6), D22.9 (Ch5), J28.2, R76.2, R77.1, R78.2, R81.2, R82.2, R84.2, U27.6 (VCCB), U28.6 (VCCB), U29.6 (VCCB), U30.6 (VCCB), U31.6 (VCCB), U32.6 (VCCB), U33.6 (VCCB), U34.6 (VCCB), U35.16 (VDD_P)
/glasgow/IO_Banks/VIO_AUX: C132.1, C133.1, J27.44, U22.E4 (VCCIO_3), U22.G4 (VCCIO_3)
/glasgow/IO_Banks/Z0_N: J27.41, U22.B2 (IOL_2B)
/glasgow/IO_Banks/Z0_P: J27.39, U22.B1 (IOL_2A)
/glasgow/IO_Banks/Z1_N: J27.38, U22.C3 (IOL_4B)
/glasgow/IO_Banks/Z1_P: J27.40, U22.C4 (IOL_4A)
/glasgow/IO_Banks/Z2_N: J27.33, U22.C1 (IOL_5B)
/glasgow/IO_Banks/Z2_P: J27.35, U22.C2 (IOL_5A)
/glasgow/IO_Banks/Z3_N: J27.29, U22.D1 (IOL_8B)
/glasgow/IO_Banks/Z3_P: J27.27, U22.E1 (IOL_8A)
/glasgow/IO_Banks/Z4_N: J27.34, U22.D3 (IOL_9B)
/glasgow/IO_Banks/Z4_P: J27.32, U22.D2 (IOL_9A)
/glasgow/IO_Banks/Z5_N: J27.26, U22.E3 (IOL_10B)
/glasgow/IO_Banks/Z5_P: J27.28, U22.E2 (IOL_10A)
/glasgow/IO_Banks/Z6_N: J27.23, U22.F2 (IOL_12B)
/glasgow/IO_Banks/Z6_P: J27.21, U22.F1 (IOL_12A)
/glasgow/IO_Banks/Z7_N: J27.20, U22.F3 (IOL_13B_GBIN7)
/glasgow/IO_Banks/Z7_P: J27.22, U22.F4 (IOL_13A)
/glasgow/IO_Banks/Z8_N: J27.17, U22.G2 (IOL_14B)
/glasgow/IO_Banks/Z8_P: J27.15, U22.G1 (IOL_14A_GBIN6)
/glasgow/IO_Banks/Z9_N: J27.14, U22.H3 (IOL_17B)
/glasgow/IO_Banks/Z9_P: J27.16, U22.G3 (IOL_17A)
/glasgow/IO_Banks/Z10_N: J27.11, U22.H2 (IOL_18B)
/glasgow/IO_Banks/Z10_P: J27.9, U22.H1 (IOL_18A)
/glasgow/IO_Banks/Z11_N: J27.3, U22.K1 (IOL_23B)
/glasgow/IO_Banks/Z11_P: J27.5, U22.J1 (IOL_23A)
/glasgow/IO_Banks/Z12_N: J27.10, U22.J2 (IOL_25B)
/glasgow/IO_Banks/Z12_P: J27.8, U22.K2 (IOL_25A)
/glasgow/IO_Banks/~SYNC: D16.1 (K), J26.2, R64.1, R65.1
/glasgow/LED_ACT: R56.1, U19.49 (PD4/FD12)
/glasgow/LED_CY: R54.1, U19.47 (PD2/FD10)
/glasgow/LED_ERR: R57.1, U19.50 (PD5/FD13)
/glasgow/LED_FPGA: R55.1, U19.48 (PD3/FD11)
/glasgow/OE: U19.35 (PA2/SLOE), U22.L3 (IOB_71)
/glasgow/PKTEND: U19.39 (PA6/PKTEND), U22.L1 (IOB_56)
/glasgow/RD: U19.1 (RDY0/SLRD), U22.J5 (IOB_78)
/glasgow/SCL: A1.142 (I2C5_SCL), R45.1, TP8.1 (1_1), TP16.1 (1_1), U19.15 (SCL), U20.6 (SCL), U21.6 (SCL), U22.H9 (IOB_104_CBSEL1), U35.14 (SCL), U37.5 (SCL), U38.5 (SCL)
/glasgow/SDA: A1.144 (I2C5_SDA), R44.1, TP7.1 (1_1), TP15.1 (1_1), U19.16 (SDA), U20.5 (SDA), U21.5 (SDA), U22.J8 (IOB_91), U35.15 (SDA), U37.4 (SDA), U38.4 (SDA)
/glasgow/VCCPLL0: C112.1, C115.1, R50.1, U22.J6 (VCCPLL0)
/glasgow/VCCPLL1: C113.1, C116.1, R51.1, U22.C6 (VCCPLL1)
/glasgow/VUSB: C96.1, FB2.2, U18.1 (EN), U18.3 (IN)
/glasgow/WR: U19.2 (RDY1/SLWR), U22.J4 (IOB_64)
/glasgow/XTALIN: C101.1, U19.5 (XTALIN), Y2.1
/glasgow/XTALOUT: C100.1, U19.4 (XTALOUT), Y2.3
/glasgow/xVBUS: F3.2, FB2.1, TP10.1 (1_1)
/glasgow/~ALERT: D26.1, R48.1, U19.33 (PA0/~INT0), U22.K4 (IOB_73)
/glasgow/~CY_RESET: C130.1, D13.3, R59.2, U19.42 (~RESET)
/glasgow/~FPGA_RESET: R52.2, U19.34 (PA1/~INT1), U22.L9 (~CRESET)
/glasgow/~MR: C122.1, SW1.2, U23.3 (~MR)
/~PLT_RST: A1.105 (~PLTRST), J2.52 (~PERST0), J24.50 (~PERST), J31.52 (~PERST0), J34.52 (~PERST0), U14.19 (PERSTB)
/~PWR_LED/~PSON: A1.5 (SLS_S0), R137.1, R408.1
/~WAKE: A1.103 (~WAKE), J2.55 (~PEWAKE0), J24.54 (~PEWAKE), J31.55 (~PEWAKE0), J34.55 (~PEWAKE0)
GND: A1.11 (GND), A1.14 (GND), A1.17 (GND), A1.20 (GND), A1.23 (GND), A1.26 (GND), A1.29 (GND), A1.32 (GND), A1.35 (GND), A1.38 (GND), A1.41 (GND), A1.44 (GND), A1.47 (GND), A1.50 (GND), A1.53 (GND), A1.56 (GND), A1.59 (GND), A1.62 (GND), A1.65 (GND), A1.68 (GND), A1.71 (GND), A1.74 (GND), A1.77 (GND), A1.80 (GND), A1.83 (GND), A1.86 (GND), A1.89 (GND), A1.92 (GND), A1.95 (GND), A1.98 (GND), A1.101 (GND), A1.107 (GND), A1.110 (GND), A1.113 (GND), A1.116 (GND), A1.135 (GND), A1.136 (GND), A1.151 (GND), A1.158 (GND), A1.167 (GND), A1.170 (GND), A1.181 (GND), A1.182 (GND), A1.188 (GND), A1.189 (GND), A1.194 (GND), A1.195 (GND), A1.200 (GND), A1.201 (GND), A1.206 (GND), A1.207 (GND), A1.212 (GND), A1.213 (GND), A1.218 (GND), A1.219 (GND), A1.224 (GND), A1.225 (GND), A1.230 (GND), A1.231 (GND), A1.236 (GND), A1.237 (GND), A1.242 (GND), A1.243 (GND), A1.248 (GND), A1.249 (GND), A1.MP (Mountinge_Pads), A2.3 (GND), A2.8 (GND), A2.13 (GND), A2.18 (GND), A2.23 (GND), A2.28 (GND), A2.38 (GND), BT1.2 (-), C1.2, C2.1, C3.1, C4.1, C5.1, C6.1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
unnamed: A1.12 (SIO_UART_RX), J1.2
unnamed: A1.10 (SIO_UART_TX), J1.1
unnamed: A1.185 (TCP1_HPD), R1.2
unnamed: A1.133 (~BIOS_SEL), TP1.1 (1_1)
unnamed: A2.39 (VSYS), J5.1 (Pin_1_1)
unnamed: BT1.1 (+), R3.2
unnamed: C43.1, R19.2
unnamed: C43.2, L1.1, U4.7 (SW), U4.8 (SW), U4.9 (SW)
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
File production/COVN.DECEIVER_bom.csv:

Designator,Footprint,Quantity,Value,LCSC Part #
A1,LattePanda_Module_H8.0mm_Horizontal,1,LattePanda_Mu,ASAA821-EASB0-7H
A2,RaspberryPi_Pico_Common_THT,1,RaspberryPi_Pico_W,
BT1,Battery_Holder_CR1220_S8411-45R,1,Battery_Cell,BS-12-B3AA003
"C1, C102, C103, C104, C105, C106, C107, C108, C110, C111, C114, C115, C116, C117, C119, C120, C121, C122, C124, C125, C130, C131, C132, C134, C135, C136, C137, C138, C139, C140, C141, C142, C143, C144, C145, C146, C147, C148, C149, C150, C151, C153, C155, C156, C157, C158, C187, C188, C189, C190, C191, C192, C193, C194, C196, C198, C199, C201, C203, C207, C209, C401, C405, C414, C415, C501, C524, C526, C527, C65, C66, C67, C68, C69, C70, C71, C72, C73, C74, C75, C77, C80, C83, C84, C91, C93, C96, C97, C98, C99",0402,90,u1,C1005X7R1H104K050BE
"C10, C12, C403, C404, C408, C523, C8, C85, C87, C9",0805,10,22u,GRM21BR61E226ME44L
"C100, C101",0402,2,9p,AC0402CRNPO9BN9R0
"C109, C112, C113, C118, C126, C127, C128, C129, C133, C152, C159, C528, C95",0805,13,4u7,GRM21BR61H475KE51L
"C11, C14, C16, C18, C20, C22, C24, C27, C29, C31, C33, C35, C37, C39",C_0402,14,u1,C1005X7R1H104K050BE
C123,CP_Elec_6.3x5.9,1,150u,A765EB157M1ALAE022
"C13, C15, C17, C19, C21, C26, C28, C30, C32, C34, C36, C38",C_0402,12,10n,  C0402C103K5RACTU
C154,0402,1,1n 50V C0G,GCM1555C1H102JA16J
"C185, C186, C204, C205, C49, C50, C511, C513, C519, C521, C88, C89",0402,12,220n,GCM155R71C224KE02D
"C195, C197, C2, C200, C202, C206, C208, C3, C4, C5, C6, C76, C90, C92",C_0603,14,10u,GRM188R61E106KA73D
"C23, C25",C_0402,2,10n,C0402C103K5RACTU
"C40, C41, C42",0402,3,1u,GRM155C81E105KE11D
"C402, C503, C504, C529, C530",0402,5,47p,C0402C470J5GACTU
"C410, C411",0402,2,1u,490-GRM155R61H105KE05DCT-ND
"C416, C417",C_0603,2,100u,GZ1608D601TF
C43,0402,1,u1,C1005X5R1A104K050BA
"C44, C45, C46, C47, C48, C51, C52, C53",1210,8,47u,GRM32ER71A476ME15L
"C507, C509, C515, C517",0402,4,330n,490-GRM155R61H334KE01JCT-ND
"C525, C531",0603,2,10u,GRM188R61E106KA73D
"C61, C62",C_0402,2,47p,C0402C470J5GACTU
"C63, C64",C_0402,2,1u,0402ZG105ZAT2A
C7,CP_Elec_8x11.9,1,330u,A768KS337M1ELAE019
"C78, C79",0402,2,12p,CC0402JRNPO9BN120
"D1, D2, D27",DIO_RCLAMP0524PATCT,3,RCLAMP0524PATCT,RCLAMP0524PATCT
"D10, D17, D21",0603,3,BLU,ORH-B36G
D11,0603,1,ORA,NCD0603O1
D12,0603,1,RED,NCD0603R1
D13,SOT-323_SC-70,1,BAT54AW,BAT54AW-7-F
D16,D_SOD-523,1,ESD5Z5.0T1G,ESD5Z5.0T1G
"D18, D20",0603,2,PNK,OSK40603C1E
"D19, D9",0603,2,WHT,NCD0603W1
"D22, D23",UDFN-14_3.5x1.35mm_P0.5mm,2,TPD6E05U06RVZR,TPD6E05U06RVZR
D24,D_SOD-323,1,CDSOD323-T36S,CDSOD323-T36S
"D25, D8",0603,2,GRN,NCD0603G1
D26,SOT-323_SC-70,1,BAT54CW,BAT54CW-7-F
"D3, D37, D38, D39, D4",0402,5,0402ESDA-05N,0402ESDA-05N
D40,D_SOD-323,1,1N5819WS,1N5819WS 
"D401, D402, D501, D502, D503, D504, D505, D506",0402,8,ESD5V0B03,ESD5V0B03
"D403, D7",0603,2,LED_G,150060BS75000
F1,0805,1,6V/2A,   BSMD0805L-200 
F3,0805,1,6V/1A,BSMD0805-100-6V
F6,0603,1,6V/50mA,C7472508
FB1,0805,1,0,MCS0402HZ0000ZE100
FB2,0402,1,"600R, 0.5A",BLM15PX601SZ1D
"H5_2, H6, H7, H8",MountingHole_2.7mm_Pad_TopOnly,4,MountingHole_M2.0,
"J2, J31, J34",PCIe_M.2_Connectors_P=0.5mm_H=4.2mm_KeyE,3,Bus_M.2_Socket_E,APCI0108-P001A
J22,RJ45_UDE_RB1-125B8G1A,1,RJ45_RB1-125B8G1A,RB1-125B8G1A
J24,PCIe_M.2_Connectors_P=0.5mm_H=4.2mm_KeyM,1,Bus_M.2_Socket_M,APCI0107-P001A
J26,Molex_KK-254_1x02_P2.54mm_Horizontal,1,Conn_01x02,22-05-3021
J27,PinHeader_2x22_P1.27mm_Vertical__SMD,1,PinHeader_2x22_P1.27mm,FTS-122-01-L-DV
J28,IDC-Header_2x10_P2.54mm_Horizontal,1,IDC-Header_2x10_P2.54mm,87834-2019
J32,HDMI_Micro-D_Molex_46765-2xxx,1,HDMI_D_1.4,  0467651001
"J5, J6",PinHeader_1x01_P2.00mm_Horizontal,2,Conn_01x01_Socket,
J501,USB_C_Receptacle_Amphenol_12401610E4-2A,1,USB_C_Receptacle,12401610E4#2ACT-ND
J7,USB3_A_Molex_48393-001,1,USB3_A,0483930003
J8,TerminalBlock_MaiXu_MX126-5.0-02P_1x02_P5.00mm,1,Conn_01x02_Socket,
L1,L_Coilcraft_XAL7070-XXX,1,550nH,XAL7070-551MEB
L401,L_6.3x6.3_H3,1,6uH8,553-BMRA000606306R8MA1CT-ND
"Q11, Q401",SOT-23,2,2N7002,2N7002
"Q12, Q13, Q14",SOT-23,3,2SK3018,2SK3018
R1,R_0402,1,100K,RCS0402100KFKED
"R120, R122, R133, R136, R137, R40",R_0402,6,2K2,RCS04022K20FKED
R121,R_0402,1,1M,560112110033
"R123, R138, R142, R144, R145, R148, R37, R39",R_0402,8,0,MCS0402HZ0000ZE100
R124,R_0402,1,21K5,RCG040221K5FKED 
"R125, R126, R127, R128, R131, R132, R134, R135, R34, R35",R_0402,10,470,ERJ-2RKF4700X
"R129, R3",R_0402,2,1K,RCS04021K00JNED
"R139, R140, R146, R147, R149, R150, R30, R31",R_0402,8,10K,RCS040210K0FKED
R16,0402,1,200K,CRCW0402200KFKED
"R18, R401, R48, R501, R503, R504, R507, R510, R52, R58, R59",0402,11,100K,RCS0402100KFKED
"R19, R20, R23",0402,3,0,MCS0402HZ0000ZE100
R21,0402,1,10,CRCW040210R0FKED
"R22, R409, R46, R505, R506, R513, R53, R65, R71, R74",0402,10,10K,RCS040210K0FKED
"R25, R26",R_0402,2,2k,RCS04022K00FKED
R28,R_0402,1,887,  RC0402JR-070RL
R29,R_0402,1,500,  PNM0402E5000BST1
R32,0603,1,2K49,RK73H1JLTD2491F
R33,R_0402,1,1M,CC0402KRX7R9BB104
"R402, R514",0402,2,19K1,CRCW040219K1FKED
"R405, R406, R407, R408, R56, R57",0402,6,1K,RCS04021K00JNED
"R42, R43",0402,2,5k1,RC0402FR-075K1L
"R44, R45, R54, R55, R60, R66, R67, R68, R69, R70, R76, R78",0402,12,2k2,RCS04022K20FKED
"R50, R51",0402,2,100R,RC0402FR-13100RL
R512,0402,1,0,
"R61, R62, R63, R64",0402,4,47R,RC0402FR-1347RL
R72,0402,1,20k,RC0402FR-1320KL
R73,0402,1,470,ERJ-2RKF4700X
"R75, R77",0402,2,4R7,RC0402FR-074R7L
R80,0603,1,0R33,KDV06FR330ET
R82,0603,1,0R15,KDV06FR150ET
R83,0402,1,49k9,RC0402FR-1349K9L
R84,0402,1,59k,RC0402FR-1359KL
R85,0402,1,24k3,RC0402FR-1324K3L
R86,R_0402,1,47K,ERA-2AEB473X
R87,R_0402,1,390K,ESR01MZPF3903 
"R88, R89",R_0402,2,51,ERJ-2RKF51R0X
R90,R_0402,1,5r1,ERJ-2RKF5101X
R91,R_0402,1,48K7,TNPW040248K7BEED
"RN1, RN2, RN3, RN4",R_Array_Convex_4x0402,4,33R,YC124-JR-1333RL
"RN5, RN6",R_Array_Convex_4x0402,2,10k,YC124-JR-0710KL
SW1,SW_Tactile_SPST_Angled_TC-1109DE,1,RST,TC-1109DE-B-F
"SW401, SW402",SW_PUSH_6mm,2,SW_Push, 450-1644-ND
"TP22, TP23, TP24, TP25",TestPoint_Pad_D2.0mm,4,TestPoint,
U1,ST_144_ADI,1,ADV7623BSTZ,ADV7623BSTZ
"U12, U13, U15, U16, U501, U503",Diodes_UDFN-10_1.0x2.5mm_P0.5mm,6,ULC0524P,ULC0524P
U14,QFN-32-1EP_4x4mm_P0.4mm_EP2.65x2.65mm,1,RTL8111H-CG-RH,RTL8111H-CG-RH
U18,SOT-23-6,1,TPD3S014,TPD3S014DBVR
U19,Cypress_QFN-56-1EP_8x8mm_P0.5mm_EP6.22x6.22mm_ThermalVias,1,CY7C68013A-56LTX,CY7C68013A-56LTXC
U20,TSSOP-8_4.4x3mm_P0.65mm,1,CAT24M01X,CAT24M01YI−GT3
U21,TSSOP-8_4.4x3mm_P0.65mm,1,BL24C256A-SFRC,BL24C256A-SFRC
U22,BGA-121_9.0x9.0mm_Layout11x11_P0.8mm_Ball0.4mm_Pad0.35mm_NSMD,1,ICE40HX8K-BG121,ICE40HX8K-BG121
U23,SOT-143,1,APX811-40UG-7,APX811-40UG-7
U24,DFN-6-1EP_2x2mm_P0.65mm_EP1x1.6mm_ThermalVias,1,TLV75533PDRVR,TLV75533PDRVR
U25,DFN-6-1EP_2x2mm_P0.65mm_EP1x1.6mm_ThermalVias,1,TLV73312PQDRVR,TLV73312PQDRVRQ1
"U26, U27, U28, U29, U30, U31, U32, U33, U34",SOT-363_SC-70-6,9,SN74LVC1T45DCKR,SN74LVC1T45DCKR
U3,DWP20_3P81X2P79,1,TPPM0110DWPR,TPPM0110DWPR
U35,TSSOP-16_4.4x5mm_P0.65mm,1,PCA6408APW,PCA6408APW
U36,SOT-23-5,1,TPS73101DBV,TPS73101DBVR
U37,SOT-23-6,1,DAC081C081CIMK,DAC081C081CIMK/NOPB
U38,VSSOP-10_3x3mm_P0.5mm,1,INA233,INA233AIDGSR
U4,VAN0019A-MFG,1,TPS548A23VANR,TPS548A23VANR
U403,TSOT-23-6,1,AP63200WU,AP63200WU
"U43, U44",Diodes_UDFN-10_1.0x2.5mm_P0.5mm,2,TPAZ1023-04F,TPAZ1023-04F
U506,IC_LM73100RPWR,1,LM73100RPWR,LM73100RPWR
U507,DFN-8-1EP_3x2mm_P0.5mm_EP1.75x1.45mm,1,AT25DN512C-MAHF-T,AT25DN512C-MAHF-T
U508,IC_TPS65987DDHRSHR,1,TPS65988DHRSHR,TPS65988DHRSHR
Y1,Crystal_SMD_3225-4Pin_3.2x2.5mm,1,25MHz,C9900024673
Y2,Crystal_SMD_3225-4Pin_3.2x2.5mm,1,24M,JF4024M00009T8188070
Y3,CRYSTAL_ABM8G_ABR,1,ABM8G-28.63636MHZ-18-D2Y-T,ABM8G-28.63636MHZ-18-D2Y-T
